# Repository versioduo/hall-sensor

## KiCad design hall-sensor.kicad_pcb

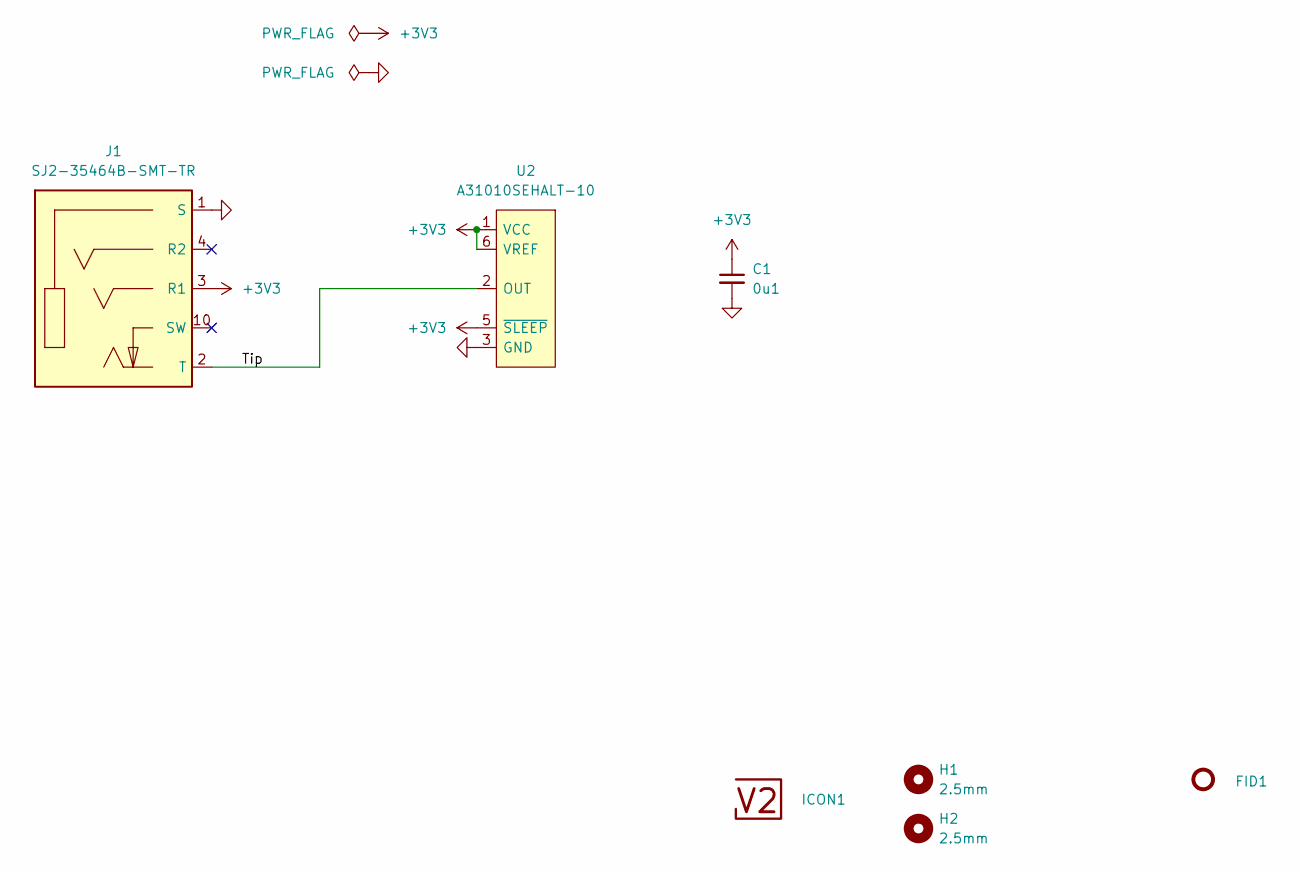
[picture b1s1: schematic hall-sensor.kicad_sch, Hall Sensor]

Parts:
C1: 0u1; C_0603; Rating 50V; Mouser 810-CGA3E2X7R1H104MA
FID1: Fiducial_Paste; Fiducial_0.5mm_Mask1mm_Paste
H1, H2: 2.5mm; MountingHole_2.5mm
ICON1: V2-logo; Logo_Small
J1: SJ2-35464B-SMT-TR; CUI_SJ2-35464B-SMT-TR; Mouser 490-SJ2-35464BSMT-TR
U2: A31010SEHALT-10; A31010SEHALT10; Mouser 250-A31010SEHALT-10

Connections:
+3V3: C1.1, J1.3 (R1), U2.1 (VCC), U2.5 (~SLEEP), U2.6 (VREF)
/Tip: J1.2 (T), U2.2 (OUT)
GND: C1.2, J1.1 (S), U2.3 (GND)

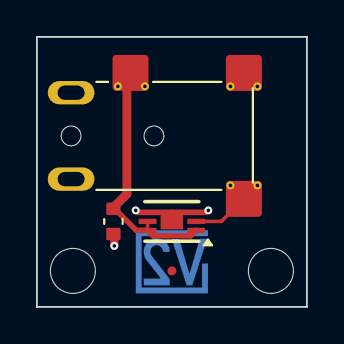
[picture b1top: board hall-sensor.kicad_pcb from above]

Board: 2 copper layers, 15.0 x 15.0 mm, 7 parts (1 on the bottom side), 3 nets.

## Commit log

2025-12-29 Import
2026-02-15 Update Library
2026-05-11 Good Bye Imperial
